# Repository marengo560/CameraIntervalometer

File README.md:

# Camera Intervalometer
Camera intervalometer for DSLR cameras

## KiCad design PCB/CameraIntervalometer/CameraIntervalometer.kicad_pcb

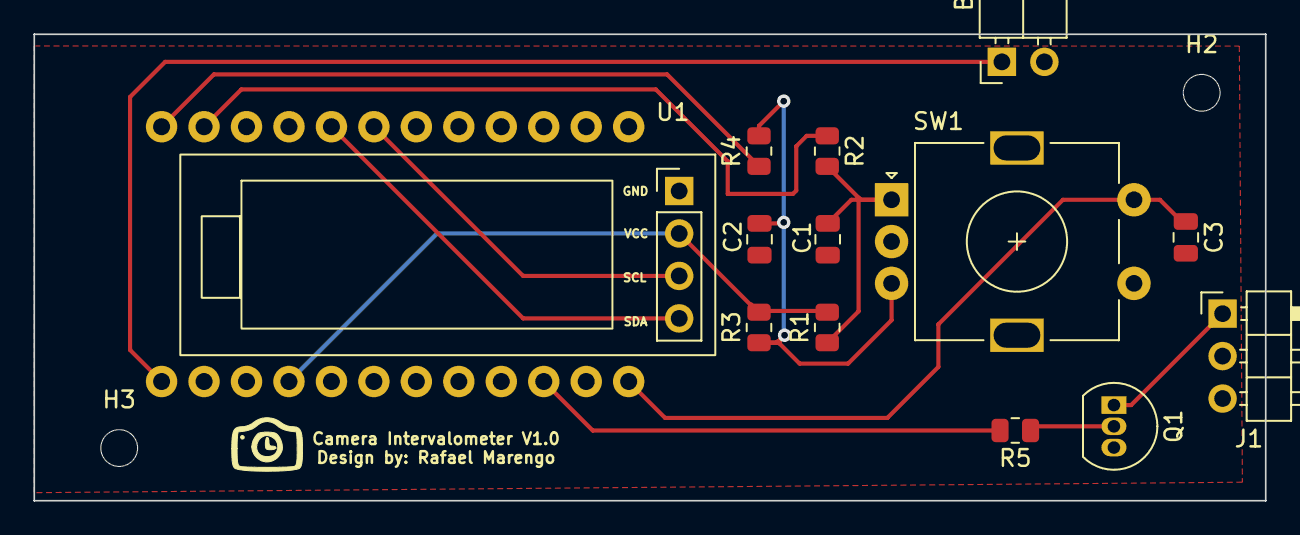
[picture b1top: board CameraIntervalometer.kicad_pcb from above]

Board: 2 copper layers, 73.7 x 27.9 mm, 16 parts (1 on the bottom side), 13 nets.

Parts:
B1: PRO MICRO; SPARKFUN_PRO_MICRO
BT1: Battery-header; PinHeader_1x02_P2.54mm_Horizontal
C1, C2, C3: 10n; C_0805_2012Metric
H2, H3: MountingHole; MountingHole_2.2mm_M2_DIN965
J1: 2.5mm_Audio_jack; PinHeader_1x03_P2.54mm_Horizontal
Q1: BC337; TO-92_Inline
R1, R2, R3, R4: 10k; R_0805_2012Metric
R5: 1K; R_0805_2012Metric
SW1: Rotary_Encoder_Switch; RotaryEncoder_Alps_EC11E-Switch_Vertical_H20mm
U1: ssd1306_oled_128x32; OLED-128x32

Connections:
+5VD: B1.21 (VCC), R1.2, R3.2, U1.2 (VCC)
/SCL: B1.6 (*3), U1.3 (SCL)
/SDA: B1.5 (2), U1.4 (SDA)
GND: B1.3 (GND), B1.4 (GND), B1.23 (GND), BT1.2 (BAT-), C1.2, C2.2, C3.2, J1.3 (GND), Q1.3 (E), SW1.C, SW1.S1, U1.1 (GND)
unnamed: B1.1 (TXO), R4.1
unnamed: B1.2 (RXI), R2.1
unnamed: B1.15 (12(MISO)), R5.2
unnamed: B1.24 (RAW), BT1.1 (BAT+)
unnamed: C1.1, R1.1, R2.2, SW1.A
unnamed: C2.1, R3.1, R4.2, SW1.B
unnamed: B1.13 (*10), C3.1, SW1.S2
unnamed: J1.1, Q1.1 (C)
unnamed: Q1.2 (B), R5.1

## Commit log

2022-04-09 Create HardwareTest.ino
    First commit
2022-04-27 First Commit
    First Commit
2022-07-20 PCB correction
    Corrected details on PCB layout
2022-08-07 Schematics and code added
    Adding schematics, gerbers and working code
